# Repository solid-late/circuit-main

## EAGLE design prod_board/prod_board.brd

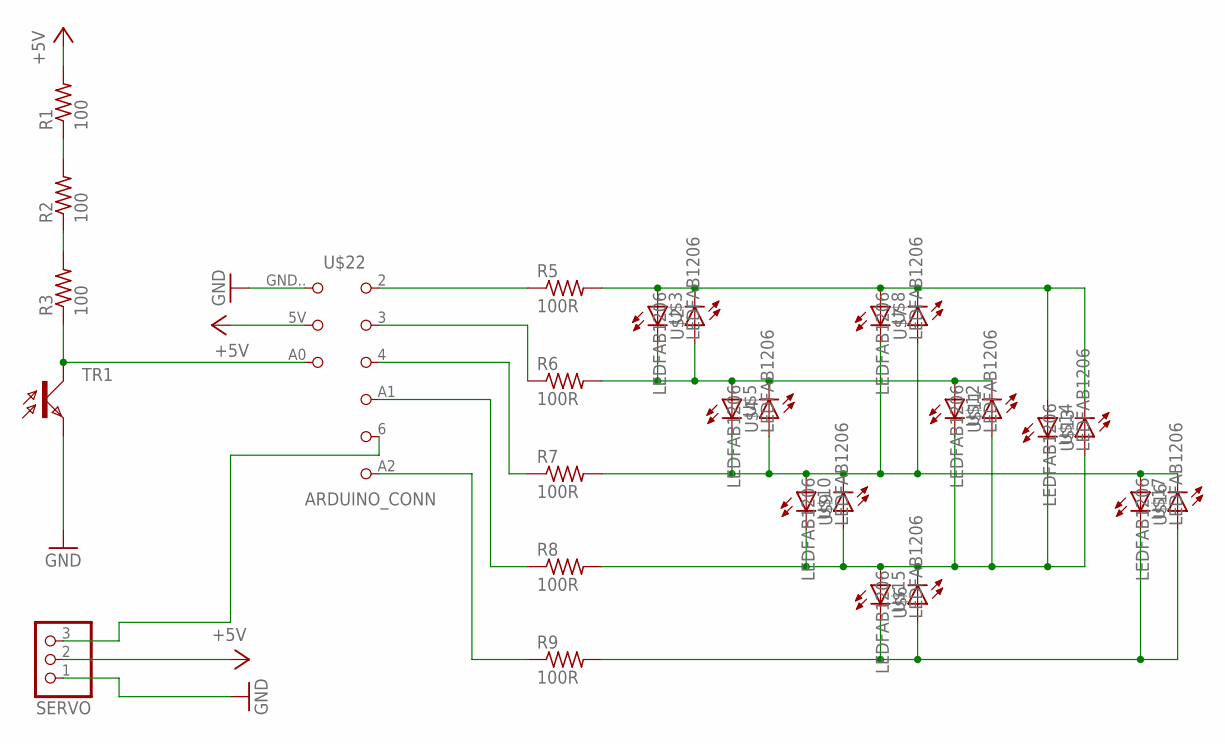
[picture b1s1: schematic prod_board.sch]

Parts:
R1, R2, R3: 100; R1206FAB
R5, R6, R7, R8, R9: 100R; R1206FAB
SERVO: PINHD-1X3; 1X03
TR1: PHOTOTRANSISTOR-NPN1206; OP1206
U$2, U$3, U$4, U$5, U$6, U$7, U$8, U$9, U$10, U$11, U$12, U$13, U$14, U$15, U$16, U$17: LEDFAB1206; LED1206FAB
U$22: ARDUINO_CONN; ARDUINO_UNO

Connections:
+5V: R1.2, SERVO.2, U$22.5V
GND: SERVO.1, TR1.E, U$22.GND.. (GND)
unnamed: R2.1, R3.2
unnamed: R1.1, R2.2
unnamed: R5.1, U$22.2 (D2)
unnamed: R3.1, TR1.C, U$22.A0
unnamed: R5.2, U$2.1 (A), U$3.2 (C), U$7.1 (A), U$8.2 (C), U$13.1 (A), U$14.2 (C)
unnamed: R6.2, U$2.2 (C), U$3.1 (A), U$4.1 (A), U$5.2 (C), U$11.1 (A), U$12.2 (C)
unnamed: R7.2, U$4.2 (C), U$5.1 (A), U$7.2 (C), U$8.1 (A), U$9.1 (A), U$10.2 (C), U$16.1 (A), U$17.2 (C)
unnamed: R8.2, U$6.1 (A), U$9.2 (C), U$10.1 (A), U$11.2 (C), U$12.1 (A), U$13.2 (C), U$14.1 (A), U$15.2 (C)
unnamed: R6.1, U$22.3 (D3)
unnamed: R7.1, U$22.4 (D4)
unnamed: R8.1, U$22.A1 (D5)
unnamed: R9.1, U$22.A2 (D7)
unnamed: SERVO.3, U$22.6 (D6)
unnamed: R9.2, U$6.2 (C), U$15.1 (A), U$16.2 (C), U$17.1 (A)

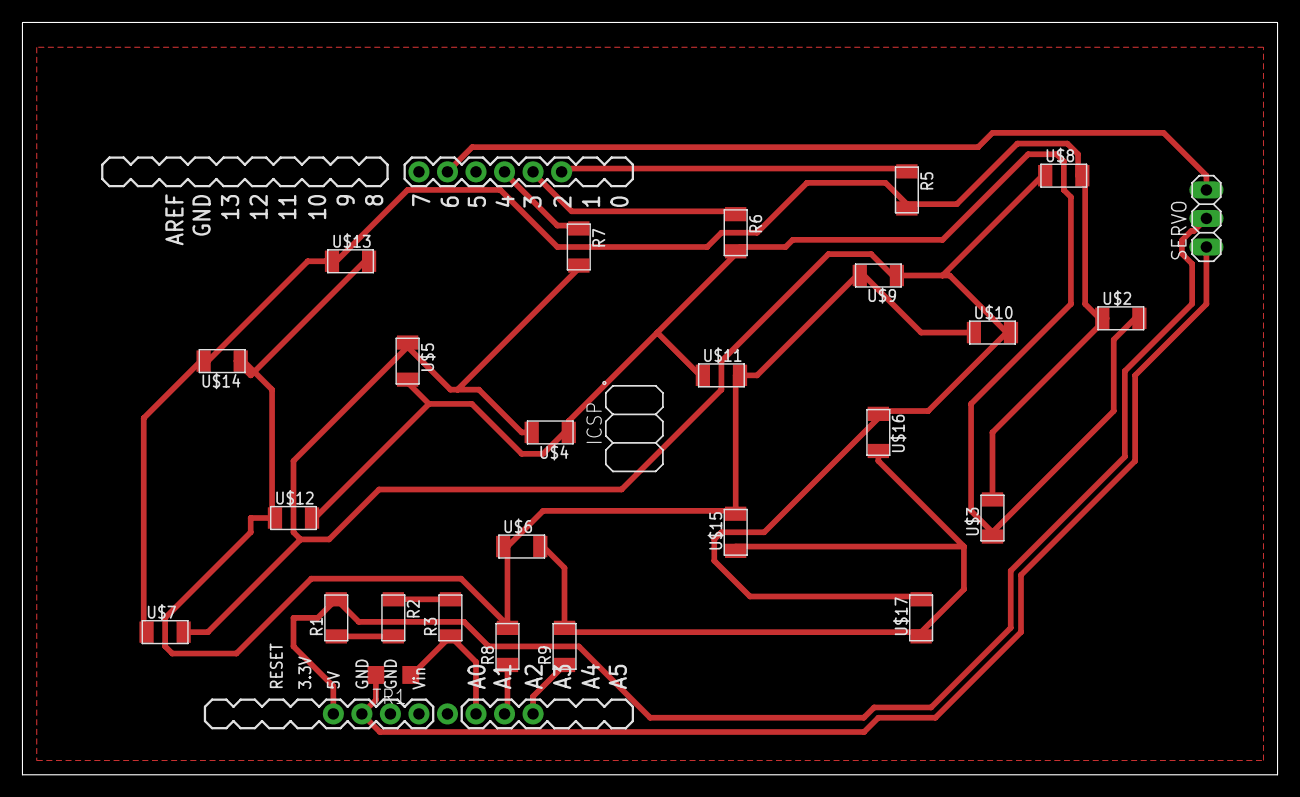
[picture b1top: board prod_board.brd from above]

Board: 2 copper layers, 111.7 x 67.0 mm, 27 parts (0 on the bottom side), 16 nets.

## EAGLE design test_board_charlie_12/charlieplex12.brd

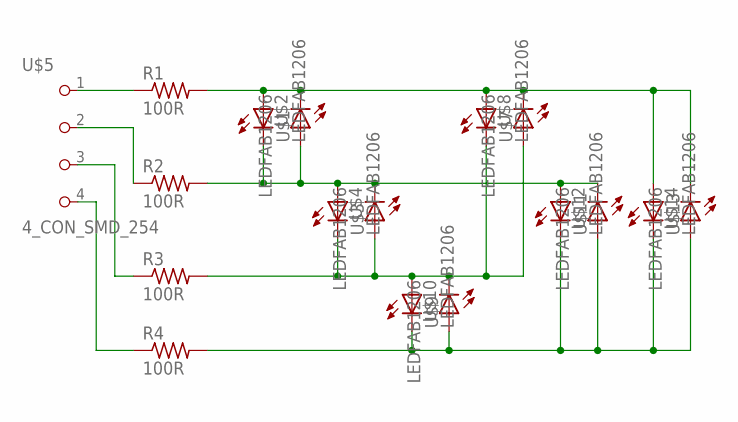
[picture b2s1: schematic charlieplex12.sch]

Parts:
R1, R2, R3, R4: 100R; R1206FAB
U$1, U$2, U$3, U$4, U$7, U$8, U$9, U$10, U$11, U$12, U$13, U$14: LEDFAB1206; LED1206FAB
U$5: 4_CON_SMD_254

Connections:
unnamed: R1.2, U$1.1 (A), U$2.2 (C), U$7.1 (A), U$8.2 (C), U$13.1 (A), U$14.2 (C)
unnamed: R2.2, U$1.2 (C), U$2.1 (A), U$3.1 (A), U$4.2 (C), U$11.1 (A), U$12.2 (C)
unnamed: R3.2, U$3.2 (C), U$4.1 (A), U$7.2 (C), U$8.1 (A), U$9.1 (A), U$10.2 (C)
unnamed: R4.2, U$9.2 (C), U$10.1 (A), U$11.2 (C), U$12.1 (A), U$13.2 (C), U$14.1 (A)
unnamed: R1.1, U$5.1
unnamed: R2.1, U$5.2
unnamed: R3.1, U$5.3
unnamed: R4.1, U$5.4

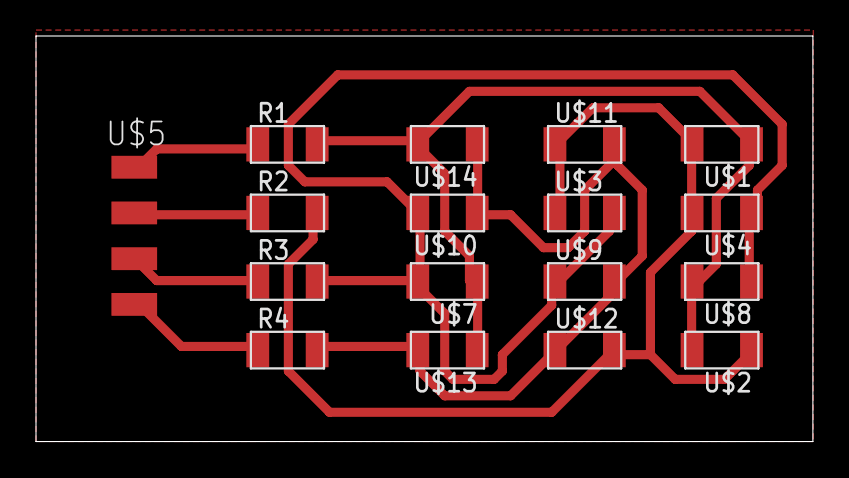
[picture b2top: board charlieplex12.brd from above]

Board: 2 copper layers, 43.2 x 22.5 mm, 17 parts (0 on the bottom side), 8 nets.

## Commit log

2018-04-25 finishing charlieplex layout
2018-04-25 restructured folders, added machining images and files
2018-05-06 added final board schematic updated to eagle 9.0.0
2018-05-06 prod board layout v1
2018-05-07 main board into production v1
2018-05-07 added instructions for the final board
